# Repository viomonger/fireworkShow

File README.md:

# fireworkShow
Project that includes hardware and software design for an expandable system to control pallets of fireworks.

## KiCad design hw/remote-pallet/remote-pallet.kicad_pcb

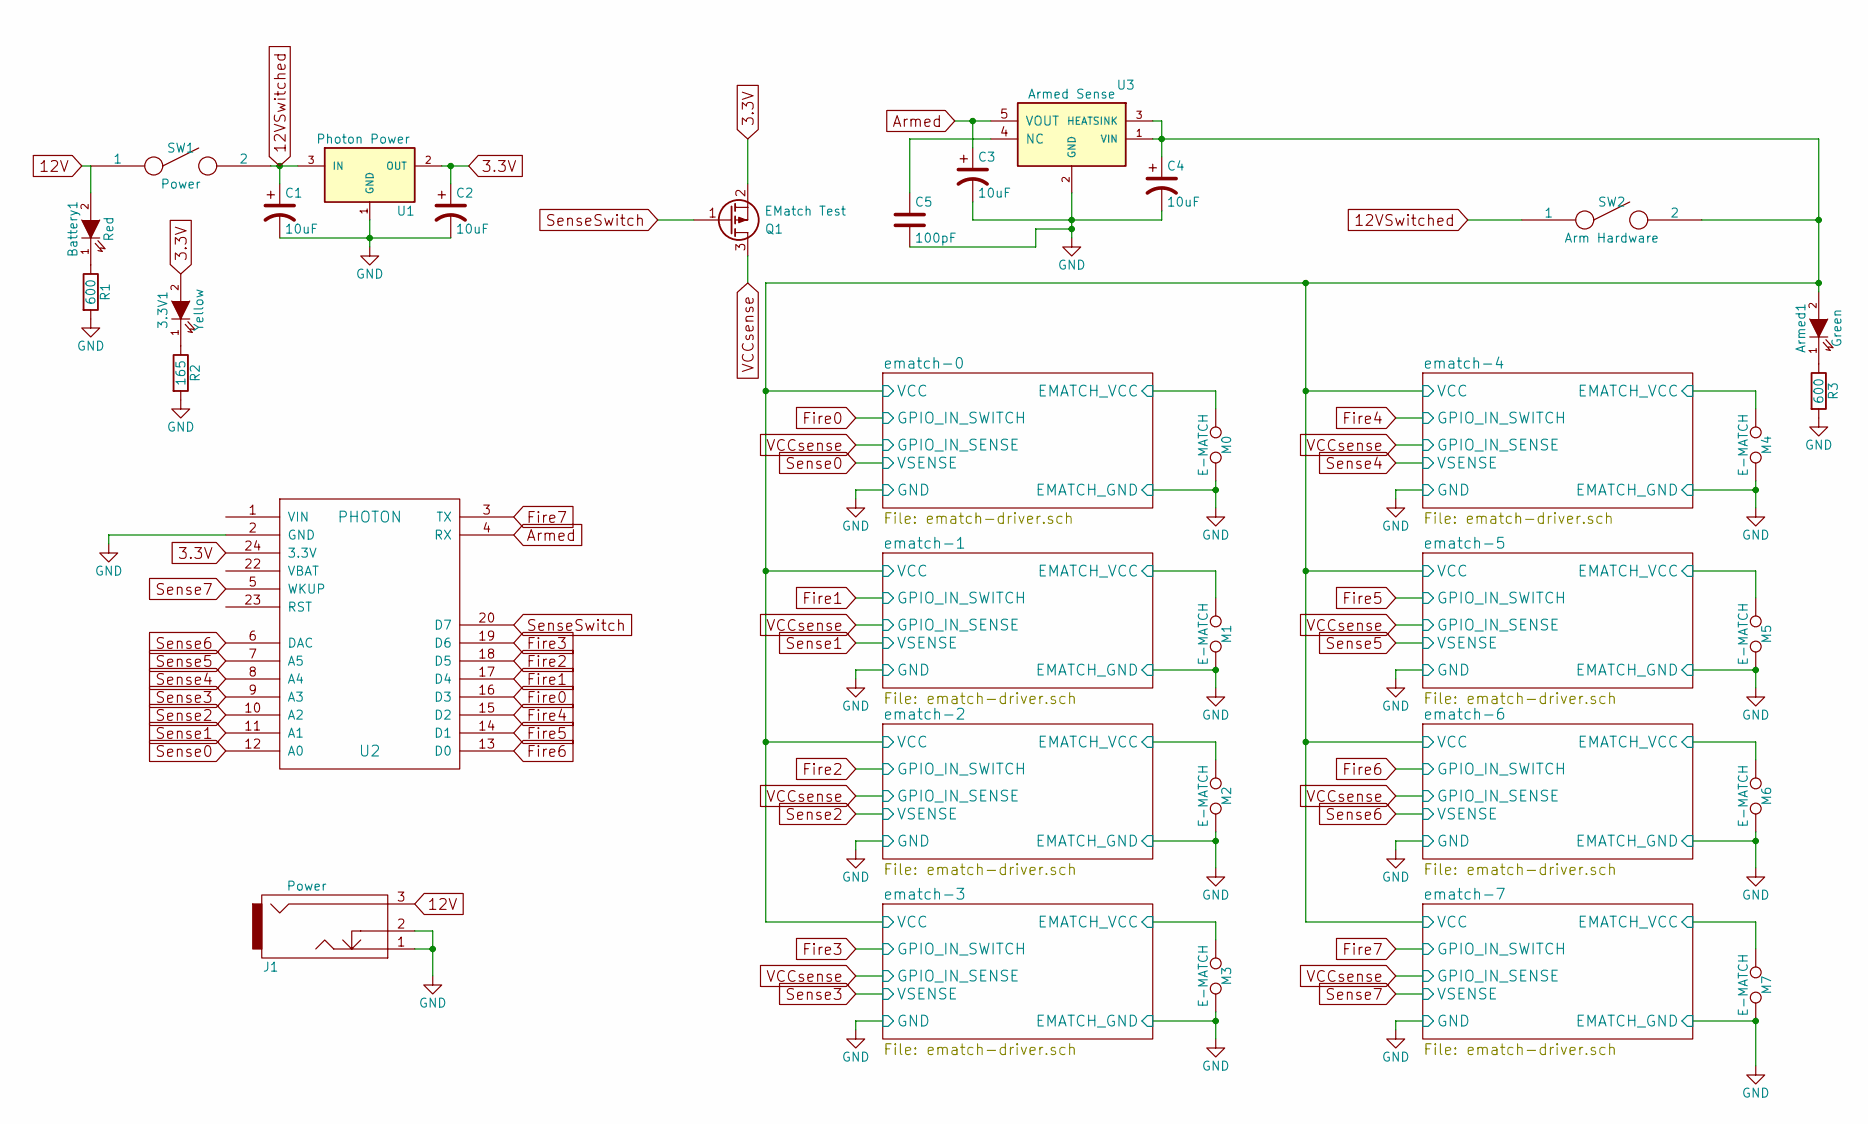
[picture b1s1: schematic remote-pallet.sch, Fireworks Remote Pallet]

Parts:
3.3V1: Yellow; LED_0603; digikey part no 732-4981-1-ND
Armed1: Green; LED_0603; digikey part no 732-4971-1-ND
Battery1: Red; LED_0603; digikey part no 732-4978-1-ND
C1, C2: 10uF; C_0805_HandSoldering; digikey part no 511-1683-1-ND
C3: 10uF; C_0805_HandSoldering; digikey part no 587-1290-1-ND
C4: 10uF; C_0805_HandSoldering; digikey part no 490-5523-1-ND
C5: 100pF; C_0805_HandSoldering
J1: Power; PJ-082BH-Barrel-Connector; digikey part no CP-082BHCT-ND
M0, M1, M2, M3, M4, M5, M6, M7: E-MATCH; TerminalBlock_Pheonix_PT-3.5mm_2pol; digikey part no ED2740-ND
Q1: EMatch Test; SOT-23; digikey part no BSS84PH6433XTMA1CT-ND
R1, R3: 600; R_0603_HandSoldering; digikey part no 311-600HCT-ND
R2: 165; R_0603_HandSoldering; digikey part no 311-165HRCT-ND
SW1: Power; M2011LL1W01; digikey part no 360-3287-ND
SW2: Arm Hardware; M2011LL1W01; digikey part no 360-3287-ND
U1: Photon Power; TO-263-3Lead; digikey part no LM1085ISX-3.3/NOPBCT-ND
U2: PHOTON
U3: Armed Sense; SOT-23-5; digikey part no AP2202K-3.3TRG1DICT-ND

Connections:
3.3V: 3.3V1.2 (A), C2.1, Q1.2 (S), U1.2 (OUT), U2.24 (3.3V)
12V: Battery1.2 (A), J1.3, SW1.1
12VSwitched: C1.1, SW1.2, SW2.1, U1.3 (IN)
/ematch-0/EMATCH_VCC: M0.1; also elsewhere on the board
/ematch-0/VCC: Armed1.2 (A), C4.1, SW2.2, U3.1 (VIN), U3.3 (HEATSINK); also elsewhere on the board
/ematch-1/EMATCH_VCC: M1.1; also elsewhere on the board
/ematch-2/EMATCH_VCC: M2.1; also elsewhere on the board
/ematch-3/EMATCH_VCC: M3.1; also elsewhere on the board
/ematch-4/EMATCH_VCC: M4.1; also elsewhere on the board
/ematch-5/EMATCH_VCC: M5.1; also elsewhere on the board
/ematch-6/EMATCH_VCC: M6.1; also elsewhere on the board
/ematch-7/EMATCH_VCC: M7.1; also elsewhere on the board
Fire0: U2.16 (D3); also elsewhere on the board
Fire1: U2.17 (D4); also elsewhere on the board
Fire2: U2.18 (D5); also elsewhere on the board
Fire3: U2.19 (D6); also elsewhere on the board
Fire4: U2.15 (D2); also elsewhere on the board
Fire5: U2.14 (D1); also elsewhere on the board
Fire6: U2.13 (D0); also elsewhere on the board
Fire7: U2.3 (TX); also elsewhere on the board
GND: C1.2, C2.2, C3.2, C4.2, C5.2, J1.1, J1.2, M0.2, M1.2, M2.2, M3.2, M4.2, M5.2, M6.2, M7.2, R1.2, R2.2, R3.2, U1.1 (GND), U2.2 (GND), U3.2 (GND); also elsewhere on the board
unnamed: 3.3V1.1 (K), R2.1
unnamed: Armed1.1 (K), R3.1
unnamed: Battery1.1 (K), R1.1
unnamed: C5.1, U3.4 (NC)
Sense0: U2.12 (A0); also elsewhere on the board
Sense1: U2.11 (A1); also elsewhere on the board
Sense2: U2.10 (A2); also elsewhere on the board
Sense3: U2.9 (A3); also elsewhere on the board
Sense4: U2.8 (A4); also elsewhere on the board
Sense5: U2.7 (A5); also elsewhere on the board
Sense6: U2.6 (DAC); also elsewhere on the board
Sense7: U2.5 (WKUP); also elsewhere on the board
VCCsense: Q1.3 (D); also elsewhere on the board

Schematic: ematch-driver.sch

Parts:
D1: ZENER; SOD-123
D2: D; SOD-123
Q2: Q_PMOS_DGS; SOT-23
Q3: Q_NMOS_DGS; TO-252-2Lead
R9: 500; R_0603_HandSoldering
R10, R11: 10k; R_0603_HandSoldering

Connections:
/ematch-0/EMATCH_VCC: D2.1 (K), Q3.2; also elsewhere on the board
/ematch-0/VCC: Q3.3, R11.1; also elsewhere on the board
Fire0: Q2.1, R10.1; also elsewhere on the board
GND: D1.2 (A), Q2.2, R10.2; also elsewhere on the board
unnamed: Q2.3, Q3.1, R11.2
Sense0: D1.1 (K), D2.2 (A), R9.1; also elsewhere on the board
VCCsense: R9.2; also elsewhere on the board

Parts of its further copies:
D3, D5, D7, D9, D11, D13, D15: ZENER; SOD-123
D4, D6, D8, D10, D12, D14, D16: D; SOD-123
Q4, Q6, Q8, Q10, Q12, Q14, Q16: Q_PMOS_DGS; SOT-23
R12, R15, R18, R21, R24, R27, R30: 500; R_0603_HandSoldering
R13, R14, R16, R17, R19, R20, R22, R23, R25, R26, R28, R29, R31, R32: 10k; R_0603_HandSoldering

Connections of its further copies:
/ematch-0/VCC: R14.1, R17.1, R20.1, R23.1, R26.1, R29.1, R32.1; also elsewhere on the board
/ematch-1/EMATCH_VCC: D4.1 (K); also elsewhere on the board
/ematch-2/EMATCH_VCC: D6.1 (K); also elsewhere on the board
/ematch-3/EMATCH_VCC: D8.1 (K); also elsewhere on the board
/ematch-4/EMATCH_VCC: D10.1 (K); also elsewhere on the board
/ematch-5/EMATCH_VCC: D12.1 (K); also elsewhere on the board
/ematch-6/EMATCH_VCC: D14.1 (K); also elsewhere on the board
/ematch-7/EMATCH_VCC: D16.1 (K); also elsewhere on the board
Fire1: Q4.1, R13.1; also elsewhere on the board
Fire2: Q6.1, R16.1; also elsewhere on the board
Fire3: Q8.1, R19.1; also elsewhere on the board
Fire4: Q10.1, R22.1; also elsewhere on the board
Fire5: Q12.1, R25.1; also elsewhere on the board
Fire6: Q14.1, R28.1; also elsewhere on the board
Fire7: Q16.1, R31.1; also elsewhere on the board
GND: D3.2 (A), D5.2 (A), D7.2 (A), D9.2 (A), D11.2 (A), D13.2 (A), D15.2 (A), Q4.2, Q6.2, Q8.2, Q10.2, Q12.2, Q14.2, Q16.2, R13.2, R16.2, R19.2, R22.2, R25.2, R28.2, R31.2; also elsewhere on the board
unnamed 26: Q4.3, R14.2; also elsewhere on the board
unnamed 27: Q6.3, R17.2; also elsewhere on the board
unnamed 28: Q8.3, R20.2; also elsewhere on the board
unnamed 29: Q10.3, R23.2; also elsewhere on the board
unnamed 30: Q12.3, R26.2; also elsewhere on the board
unnamed 31: Q14.3, R29.2; also elsewhere on the board
unnamed 32: Q16.3, R32.2; also elsewhere on the board
Sense1: D3.1 (K), D4.2 (A), R12.1; also elsewhere on the board
Sense2: D5.1 (K), D6.2 (A), R15.1; also elsewhere on the board
Sense3: D7.1 (K), D8.2 (A), R18.1; also elsewhere on the board
Sense4: D9.1 (K), D10.2 (A), R21.1; also elsewhere on the board
Sense5: D11.1 (K), D12.2 (A), R24.1; also elsewhere on the board
Sense6: D13.1 (K), D14.2 (A), R27.1; also elsewhere on the board
Sense7: D15.1 (K), D16.2 (A), R30.1; also elsewhere on the board
VCCsense: R12.2, R15.2, R18.2, R21.2, R24.2, R27.2, R30.2; also elsewhere on the board

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
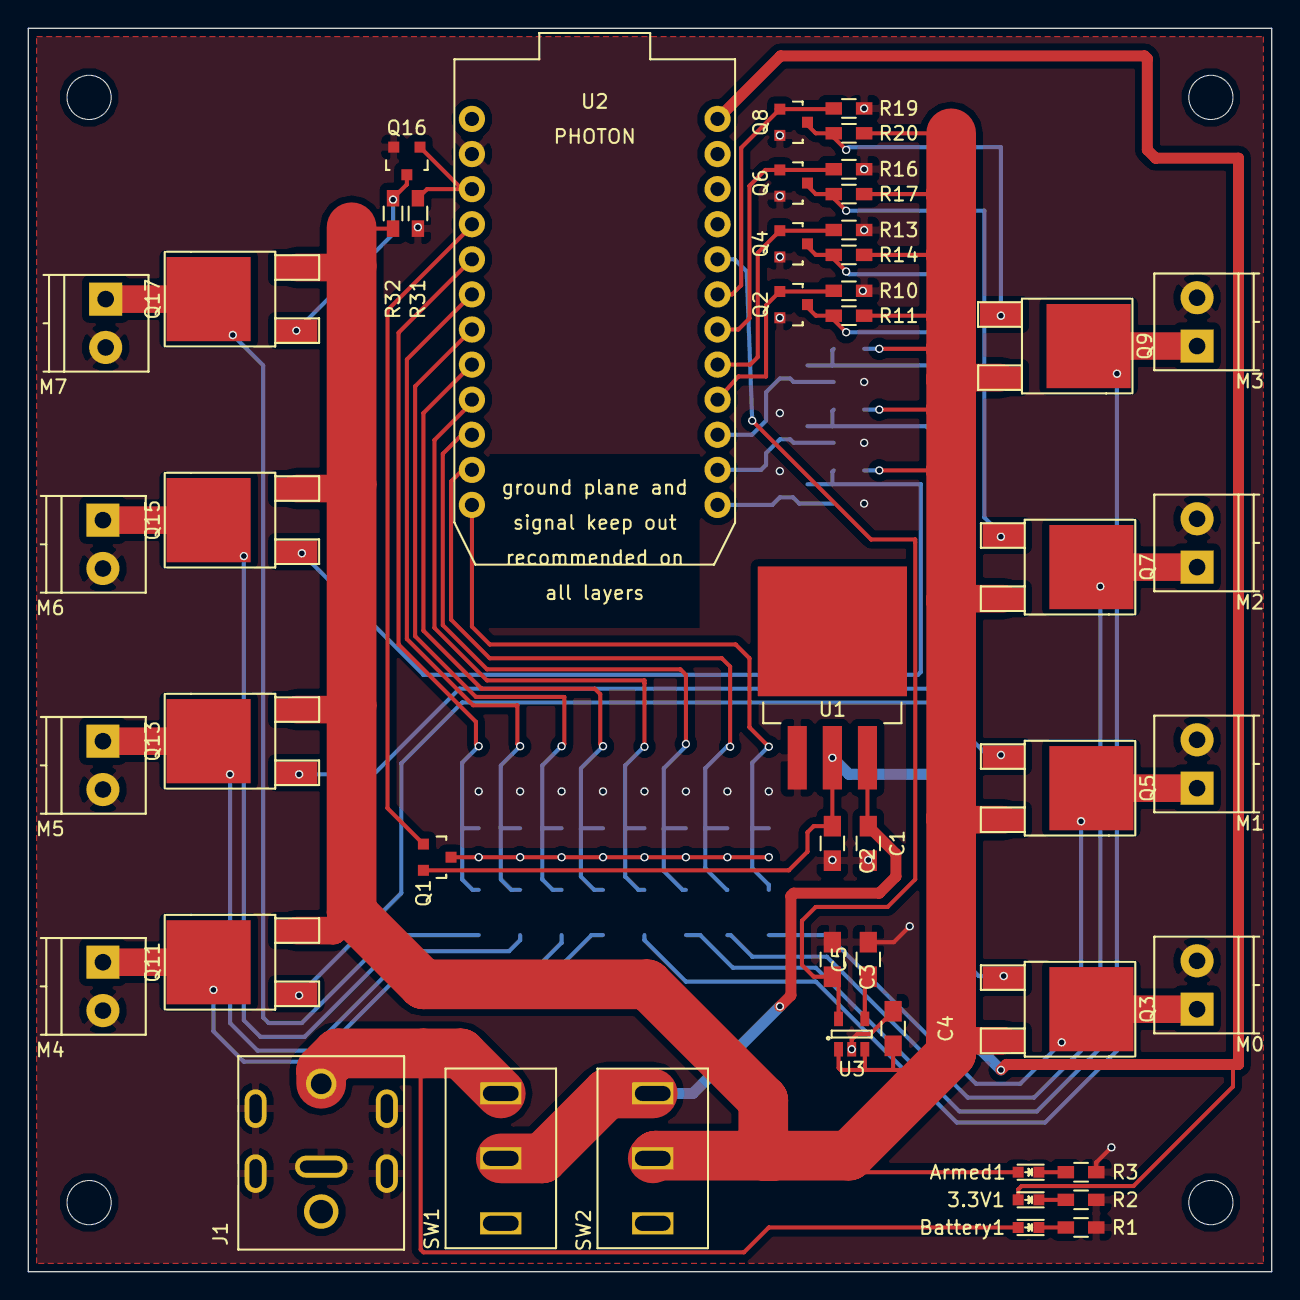
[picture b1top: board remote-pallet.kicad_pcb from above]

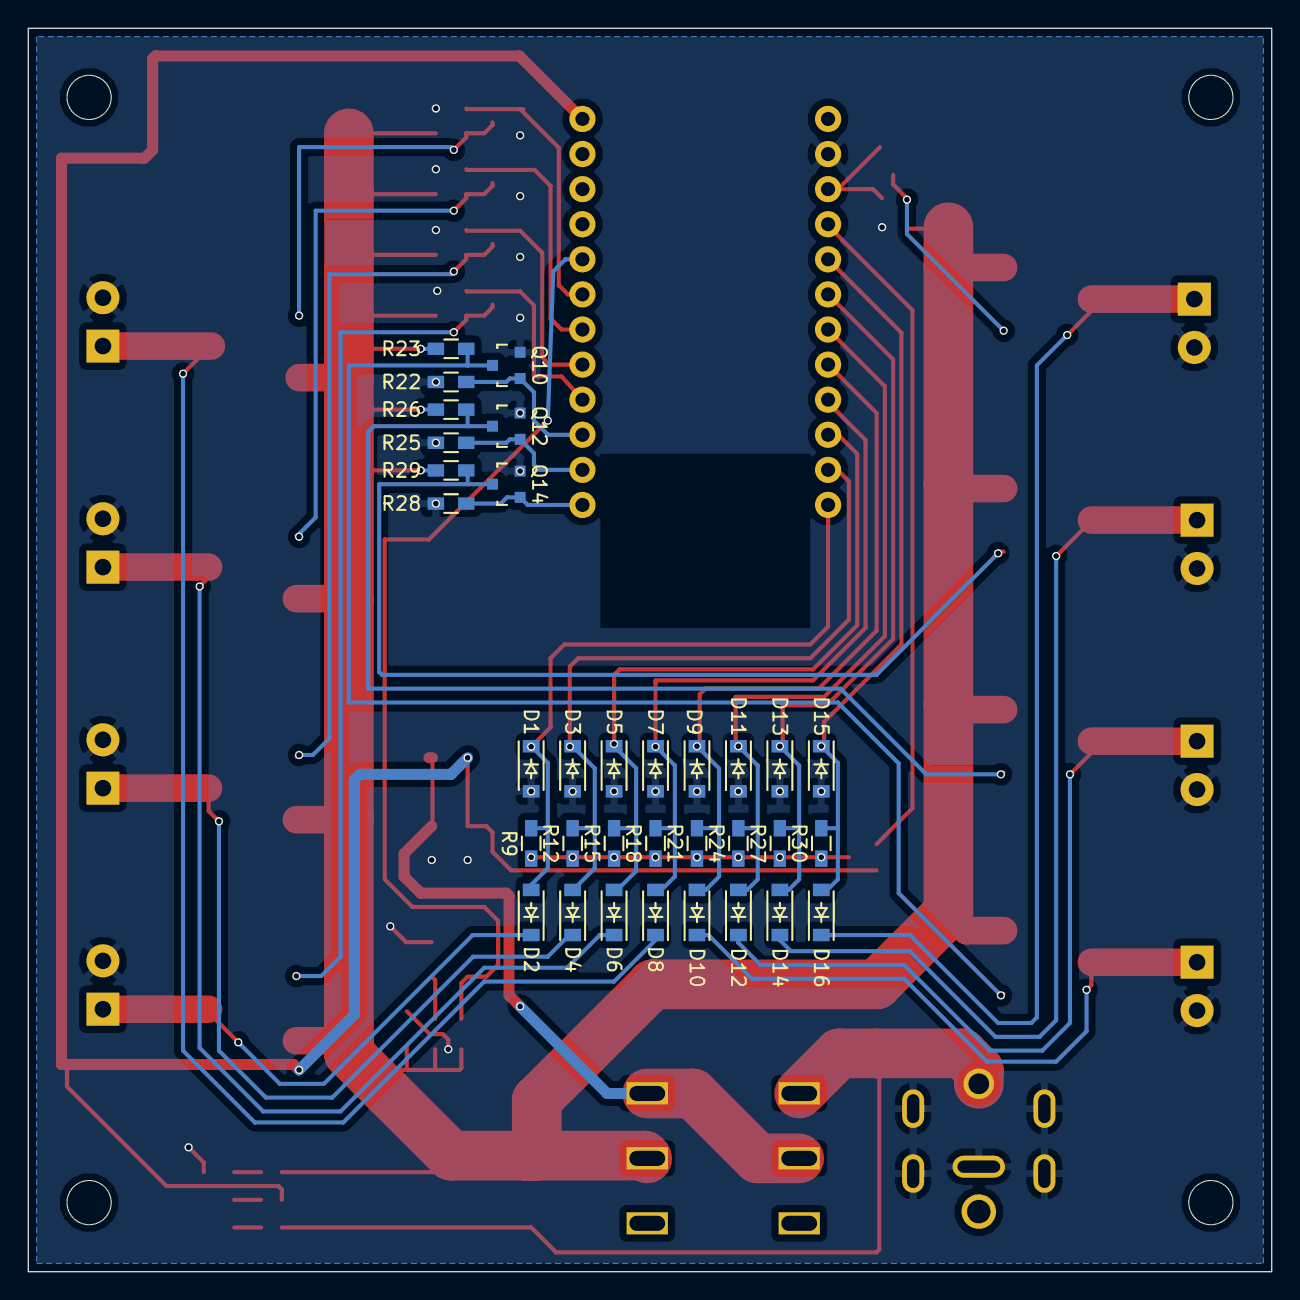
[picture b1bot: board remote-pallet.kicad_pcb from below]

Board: 2 copper layers, 90.0 x 90.0 mm, 82 parts (33 on the bottom side), 44 nets.

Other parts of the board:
Q5, Q7, Q9, Q11, Q13, Q15, Q17: Q_NMOS_GDS; TO-252-2Lead

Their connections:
/ematch-0/VCC: Q5.3, Q7.3, Q9.3, Q11.3, Q13.3, Q15.3, Q17.3; also elsewhere on the board
/ematch-1/EMATCH_VCC: Q5.2; also elsewhere on the board
/ematch-2/EMATCH_VCC: Q7.2; also elsewhere on the board
/ematch-3/EMATCH_VCC: Q9.2; also elsewhere on the board
/ematch-4/EMATCH_VCC: Q11.2; also elsewhere on the board
/ematch-5/EMATCH_VCC: Q13.2; also elsewhere on the board
/ematch-6/EMATCH_VCC: Q15.2; also elsewhere on the board
/ematch-7/EMATCH_VCC: Q17.2; also elsewhere on the board
unnamed 26: Q5.1; also elsewhere on the board
unnamed 27: Q7.1; also elsewhere on the board
unnamed 28: Q9.1; also elsewhere on the board
unnamed 29: Q11.1; also elsewhere on the board
unnamed 30: Q13.1; also elsewhere on the board
unnamed 31: Q15.1; also elsewhere on the board
unnamed 32: Q17.1; also elsewhere on the board

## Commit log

2016-01-12 Starting files
    Just a couple of files to get started and create a directory structure.
2016-01-12 Fix windows files
    Stupid windows created a file with .py.txt extension, thanks windows! :/
2016-01-18 Hardware list added
    Added description of current hardware that I have.
2016-01-18 Adding Files from SparkFun testing
    These files are from here:
    https://github.com/sparkfun/RF_Transceiver_Breakout-RFM22B
    and were used to test the transciever. A place to start for testing.
2016-02-26 Adding schemataic files.
2016-03-17 Adding new library for photon and updating the schematic files.
2016-03-17 really commiting changes to the schematic this time
2016-03-17 adding second switch
2016-03-18 updating schematic and starting board layout
2016-03-18 updating schematic and pcb
2016-03-19 adding some new footprints, laying out board
2016-03-19 Adding photon code
2016-03-20 changes to layout adding debug LEDs
2016-03-22 adding graphic and small updates to PCB
2016-03-22 updating pcb and adding part numbers for digikey
2016-04-28 updaint schematic and layout
